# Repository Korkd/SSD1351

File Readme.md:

Workshopping a breakout board for a SSD1351 128x128 OLED to mount to the left half of a BastardKB Dilemma.

## Goals

* Add slit to remove need to rotate display 180 degrees
* Take advantage of top mounting holes
* Match pinout of Dilemma

Shoutout to Jon Thomasson and [his work](https://github.com/jonthomasson/1.5OLEDBreakout) as it was a great resource.

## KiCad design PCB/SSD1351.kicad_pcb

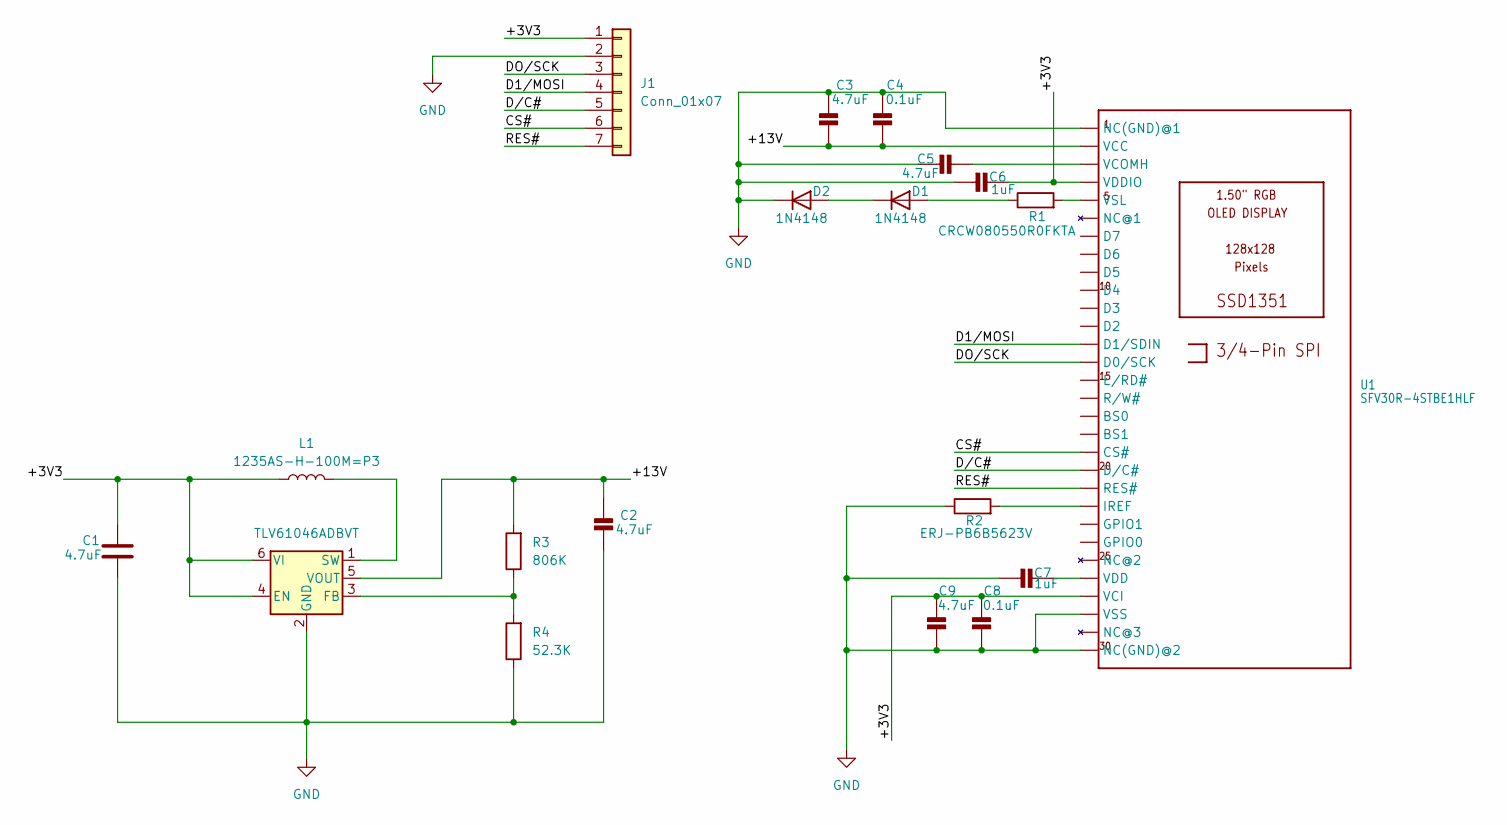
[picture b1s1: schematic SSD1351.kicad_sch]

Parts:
C1, C9: 4.7uF; C_0805_2012Metric
C2, C3, C5: 4.7uF; C_1206_3216Metric
C4, C8: 0.1uF; C_0603_1608Metric
C6, C7: 1uF; C_0805_2012Metric
D1, D2: 1N4148; D_SOD-323
J1: Conn_01x07; PinHeader_1x07_P2.54mm_Vertical
L1: 1235AS-H-100M=P3; IND_1235AS-H-100M=P3
R1: CRCW080550R0FKTA; R_0805_2012Metric
R2: ERJ-PB6B5623V; R_0805_2012Metric
R3: 806K; R_0805_2012Metric
R4: 52.3K; R_0805_2012Metric
U1: SFV30R-4STBE1HLF; CONNECTORS_FPC_SFV30R_4STBE1HLF
U2: TLV61046ADBVT; SOT-23-6

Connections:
/+3V3: C1.1, C6.1, C8.1, C9.1, J1.1, L1.1, U1.4 (VDDIO), U1.27 (VCI), U2.4 (EN), U2.6 (VI)
/+13V: C2.1, C3.2, C4.2, R3.2, U1.2 (VCC), U2.5 (VOUT)
/CS#: J1.6, U1.19 (CS#)
/D1/MOSI: J1.4, U1.13 (D1/SDIN)
/DO/SCK: J1.3, U1.14 (D0/SCK)
/D/C#: J1.5, U1.20 (D/C#)
/RES#: J1.7, U1.21 (RES#)
GND: C1.2, C2.2, C3.1, C4.1, C5.2, C6.2, C7.2, C8.2, C9.2, D2.1 (K), J1.2, R2.1, R4.1, U1.1 (NC(GND)@1), U1.28 (VSS), U1.30 (NC(GND)@2), U2.2 (GND)
unnamed: C5.1, U1.3 (VCOMH)
unnamed: C7.1, U1.26 (VDD)
unnamed: D1.2 (A), R1.1
unnamed: D1.1 (K), D2.2 (A)
unnamed: R2.2, U1.22 (IREF)
unnamed: R1.2, U1.5 (VSL)
unnamed: R3.1, R4.2, U2.3 (FB)
unnamed: L1.2, U2.1 (SW)

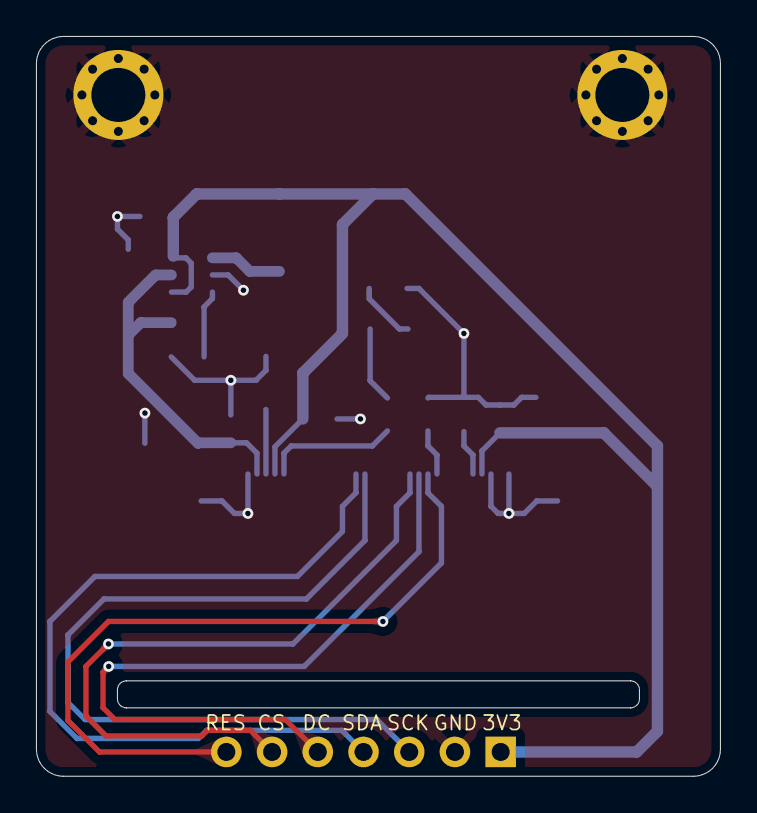
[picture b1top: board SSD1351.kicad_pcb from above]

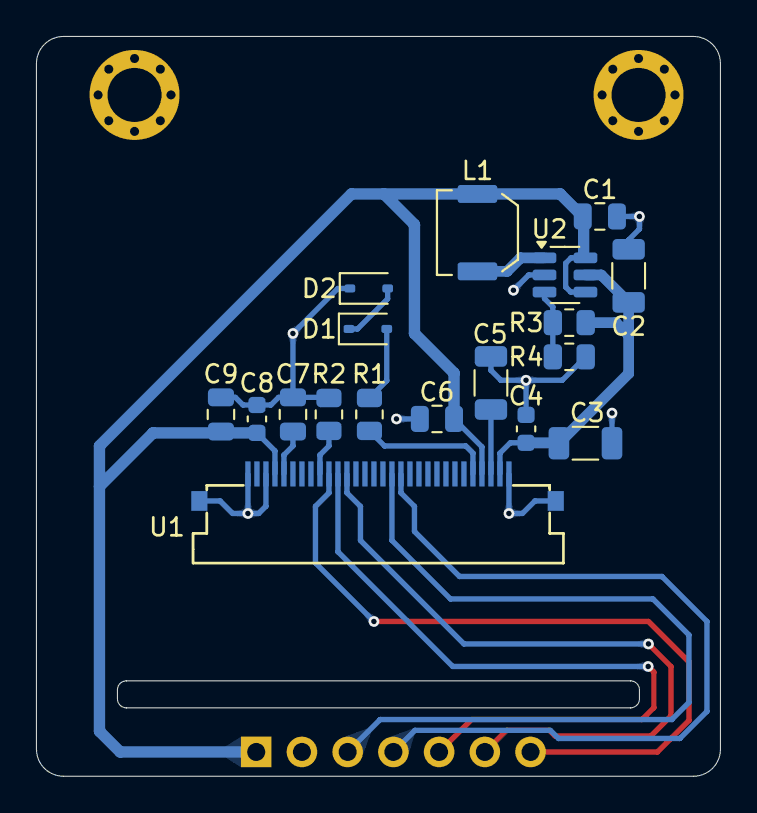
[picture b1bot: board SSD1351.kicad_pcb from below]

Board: 2 copper layers, 38.0 x 41.1 mm, 19 parts (18 on the bottom side), 16 nets.

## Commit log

2024-07-13 Adding Initial PCB
    Added KiCAD project
2024-07-13 Adding readme
2024-07-13 Correcting readme typo
2024-07-13 More readme changes
    Adding in goals for the board
2024-07-14 Added SKUs for components
2024-07-14 Adding a few more SKUs
2024-07-15 Updated PCB
    Consulted datasheets and adjusted cap ratings.
    Reworked power distribution and location.
    Started tracking down specific components and updating the BOM.
2024-07-16 Adding datasheets and more pcb design changes
    * Added datasheets for ICs
    * Removed unused footprints
    * Updated PCB to use correct sized caps
2024-07-17 Changing 13v boost converter
    Replace the FAN5331 with MIC2288 as a result of some sourcing issues. Redesigned and updated all the relevant components.
    Added in some new footprints to make hand soldering easier for inductor and boost converter.
2024-07-18 More power system changes
    Swapping out MLC2288 for TLV61046A and removing redundant diode.
    Also swapped out inductor for a more efficient one.
